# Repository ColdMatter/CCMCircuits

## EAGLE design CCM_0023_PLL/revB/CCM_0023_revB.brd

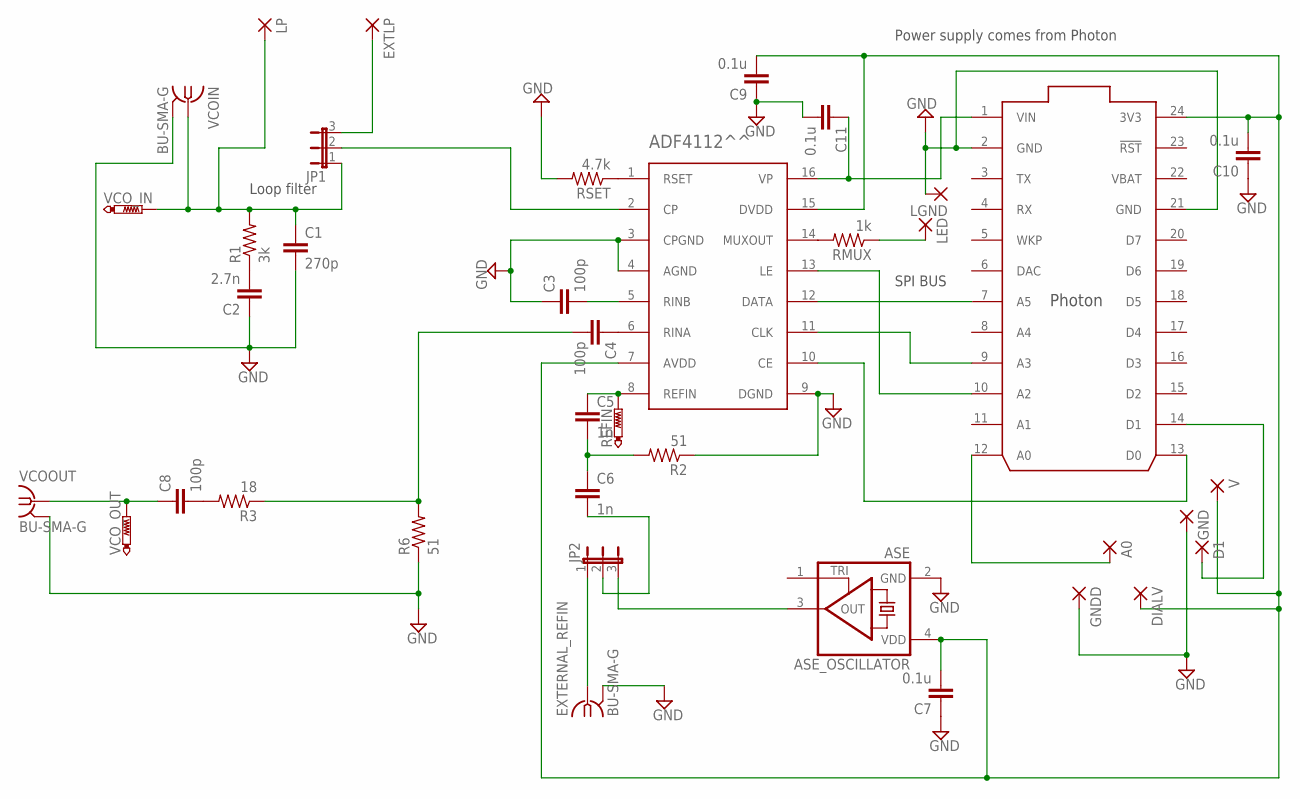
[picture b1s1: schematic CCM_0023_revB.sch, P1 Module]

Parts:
A0: 1,6/0,8
ADF4112^^: ADF4112
ASE_OSCILLATOR: ASE
C1: 270p; C0603
C2: 2.7n; C0603
C3, C4, C8: 100p; C0603
C5, C6: 1n; C0603
C7, C9, C10, C11: 0.1u; C0603
D1: 1,6/0,8
DIALV: 1,6/0,8
EXTERNAL_REFIN: BU-SMA-G
EXTLP: 1,6/0,8
GND: 1,6/0,8
GNDD: 1,6/0,8
JP1, JP2: JP2E; JP2
LED: 1,6/0,8
LGND: 1,6/0,8
LP: 1,6/0,8
PHOTON: PHOTON_WITH_HEADERS; PHOTON
R1: 3k; R0603
R2, R6: 51; R0603
R3: 18; R0603
REFIN: PTR1B2,54; B2,54
RMUX: 1k; R0603
RSET: 4.7k; R0603
V: 1,6/0,8
VCOIN: BU-SMA-G
VCOOUT: BU-SMA-G
VCO_IN: PTR1B2,54; B2,54
VCO_OUT: PTR1B2,54; B2,54

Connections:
GND: ADF4112^^.3 (CPGND), ADF4112^^.4 (AGND), ADF4112^^.9 (DGND), ASE_OSCILLATOR.2 (GND), C1.2, C2.1, C3.1, C7.1, C9.1, C10.1, C11.2, EXTERNAL_REFIN.2, EXTERNAL_REFIN.3 (2), EXTERNAL_REFIN.4 (2), EXTERNAL_REFIN.5 (2), GND.1, GNDD.1, LGND.1, PHOTON.2 (GND), PHOTON.21 (GND), R2.1, R6.1, RSET.2, VCOIN.2, VCOIN.3 (2), VCOIN.4 (2), VCOIN.5 (2), VCOOUT.2, VCOOUT.3 (2), VCOOUT.4 (2), VCOOUT.5 (2)
unnamed: ADF4112^^.12 (DATA), PHOTON.7 (A5)
unnamed: ADF4112^^.11 (CLK), PHOTON.9 (A3)
unnamed: ADF4112^^.13 (LE), PHOTON.10 (A2)
unnamed: ADF4112^^.1 (RSET), RSET.1
unnamed: C2.2, R1.1
unnamed: EXTERNAL_REFIN.1, JP2.1
unnamed: ASE_OSCILLATOR.3 (OUT), JP2.3
unnamed: ADF4112^^.8 (REFIN), C5.1, REFIN.TP
unnamed: C5.2, C6.1, R2.2
unnamed: ADF4112^^.5 (RINB), C3.2
unnamed: ADF4112^^.14 (MUXOUT), RMUX.2
unnamed: C8.1, VCOOUT.1, VCO_OUT.TP
unnamed: A0.1, PHOTON.12 (A0)
unnamed: D1.1, PHOTON.14 (D1)
unnamed: ADF4112^^.16 (VP), C11.1, PHOTON.1 (VIN)
unnamed: C8.2, R3.2
unnamed: C4.2, R3.1, R6.2
unnamed: ADF4112^^.6 (RINA), C4.1
unnamed: LED.1, RMUX.1
unnamed: ADF4112^^.7 (AVDD), ADF4112^^.15 (DVDD), ASE_OSCILLATOR.4 (VDD), C7.2, C9.2, C10.2, DIALV.1, PHOTON.24 (3V3), V.1
unnamed: EXTLP.1, JP1.3
unnamed: ADF4112^^.2 (CP), JP1.2
unnamed: ADF4112^^.10 (CE), PHOTON.13 (D0)
unnamed: C1.1, JP1.1, LP.1, R1.2, VCOIN.1, VCO_IN.TP
unnamed: C6.2, JP2.2
VBAT: PHOTON.22 (VBAT)

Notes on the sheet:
Loop filter
SPI BUS
Power supply comes from Photon

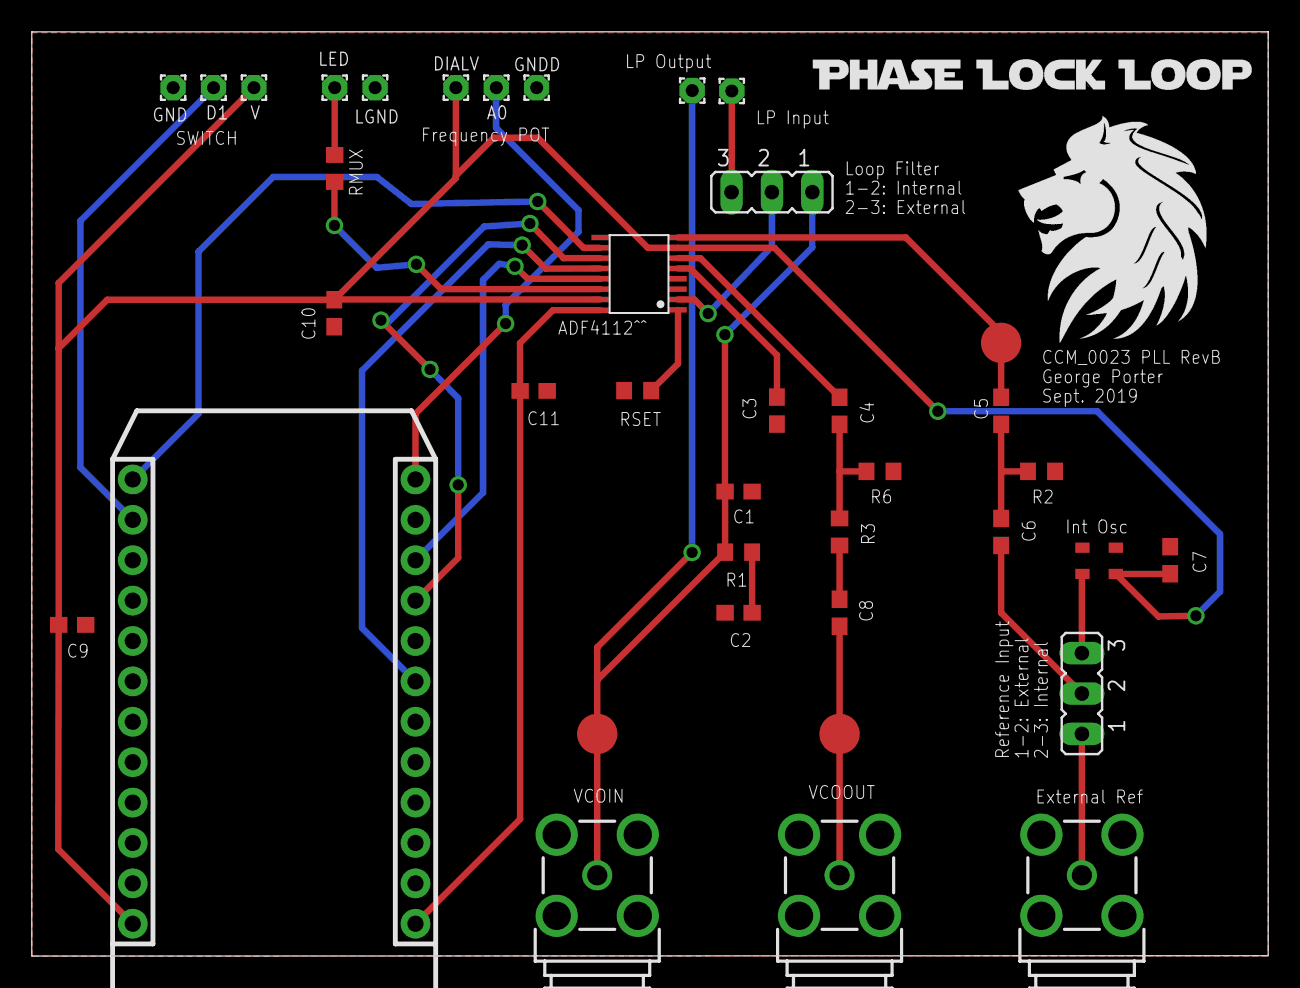
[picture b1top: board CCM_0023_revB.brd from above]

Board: 2 copper layers, 77.8 x 58.1 mm, 38 parts (0 on the bottom side), 26 nets.

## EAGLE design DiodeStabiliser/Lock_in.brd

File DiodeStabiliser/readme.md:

Diode Stabilisation Circuit

This is a work in progress circuit which aims to stabilise a laser diode 
to the centre of its mode. It works by modulating the diode current and 
lock in detecting the increased intensity noise, then feeding back to the 
current to minimise this noise. This works in conjunction with a frequency
lock. It's a copy of the work in Chiow's paper:

Extended-cavity diode lasers with tracked resonances
Sheng-wey Chiow, Quan Long, Christoph Vo, Holger Müller, and Steven Chu  »View Author Affiliations

Applied Optics, Vol. 46, Issue 33, pp. 7997-8001 (2007)
http://dx.doi.org/10.1364/AO.46.007997

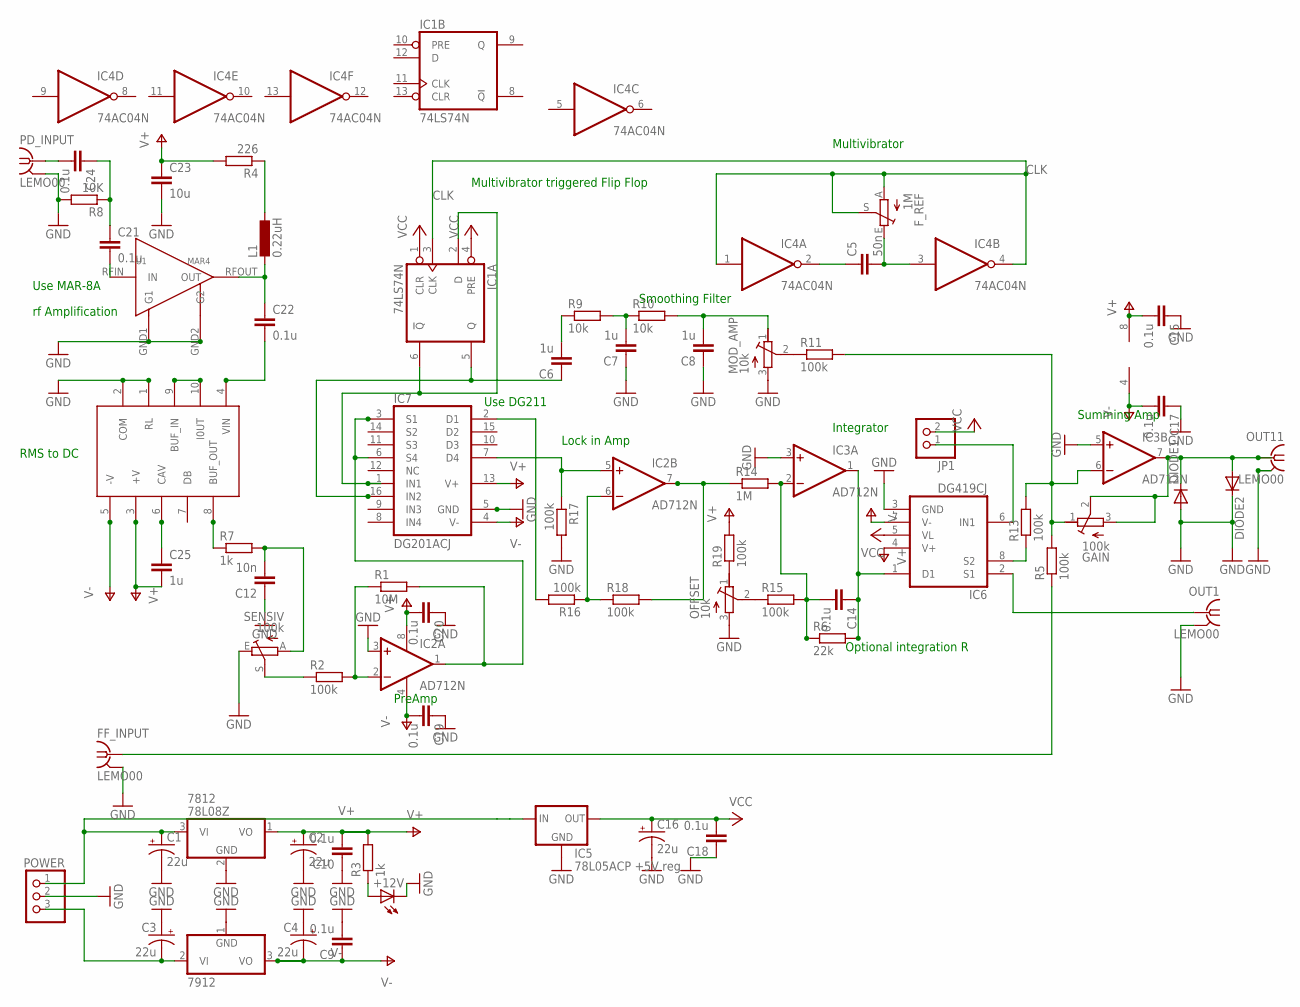
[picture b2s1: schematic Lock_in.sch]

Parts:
7812: 78L08Z; TO92
7912: 79L12Z; TO92
+12V: LED5MM
C1, C2, C3, C4, C16: 22u; E5-4
C5: 50n; C050-024X044
C6, C7, C8: 1u; C050-024X044
C9, C10, C14, C15, C17, C18, C19, C20: 0.1u; C050-024X044
C12: 10n; C050-024X044
C21, C22, C24: 0.1u; C0805
C23: 10u; C1206
C25: 1u; C0805
DIODE1, DIODE2: 1N4004; DO41-10
FF_INPUT: LEMO00; LEMOPAC.PAC
F_REF: 1M; S63P
GAIN: 100k; RTRIM43P
IC1: 74LS74N; DIL14
IC2, IC3: AD712N; DIL08
IC4: 74AC04N; DIL14
IC5: 78L05ACP +5V reg; 78LXX
IC6: DG419CJ; DIL08
IC7: DG201ACJ; DIL16
JP1: PINHD-1X2; 1X02
L1: 0.22uH; L3216C
MOD_AMP: 10k; RTRIM43P
OFFSET: 10k; RTRIM43P
OUT1, OUT11: LEMO00; LEMOPAC.PAC
PD_INPUT: LEMO00; LEMOPAC.PAC
POWER: PINHD-1X3; 1X03
R1: 10M; 0204/7
R2, R5, R11, R13, R15, R16, R17, R18, R19: 100k; 0204/7
R3, R7: 1k; 0204/7
R4: 226; R1206
R6: 22k; 0204/7
R8: 10K; R1206
R9, R10: 10k; 0204/7
R14: 1M; 0204/7
SENSIV: 100k; S63P
U1: MAR4; VV105
U$1: AD636; TO100

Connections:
CLK: F_REF.A, F_REF.S, IC1.3 (CLK), IC4.1 (I), IC4.4 (O)
F2: C6.1, IC1.5 (Q), IC7.16 (IN2)
GND: 7812.2 (GND), 7912.1 (GND), +12V.K (C), C1.-, C2.-, C3.+, C4.+, C7.1, C8.1, C9.2, C10.1, C12.1, C15.1, C16.-, C17.1, C18.1, C19.1, C20.1, C23.2, DIODE1.A, DIODE2.C, FF_INPUT.2 (GND), FF_INPUT.3 (GND), FF_INPUT.4 (GND), FF_INPUT.5 (GND), IC1.7 (GND), IC2.3 (+IN), IC3.3 (+IN), IC3.5 (+IN), IC4.7 (GND), IC5.GND, IC6.3 (GND), IC7.5 (GND), MOD_AMP.3 (E), OFFSET.3 (E), OUT1.2 (GND), OUT1.3 (GND), OUT1.4 (GND), OUT1.5 (GND), OUT11.2 (GND), OUT11.3 (GND), OUT11.4 (GND), OUT11.5 (GND), PD_INPUT.2 (GND), PD_INPUT.3 (GND), PD_INPUT.4 (GND), PD_INPUT.5 (GND), POWER.2, R8.2, R17.2, SENSIV.E, U1.GND1 (G1), U1.GND2 (G2), U$1.1 (RL), U$1.2 (COM)
GND1: IC6.6 (IN1), JP1.1
MOD_AMPLITUDE: C8.2, MOD_AMP.1 (A), R10.2
unnamed: C5.1, IC4.2 (O)
unnamed: +12V.A, R3.1
unnamed: DIODE1.C, DIODE2.A, GAIN.2 (S), GAIN.3 (E), IC3.7 (OUT), OUT11.1
unnamed: IC2.2 (-IN), R1.1, R2.2
unnamed: C5.2, F_REF.E, IC4.3 (I)
unnamed: R2.1, SENSIV.S
unnamed: C12.2, R7.2, SENSIV.A
unnamed: R7.1, U$1.8 (BUF_OUT)
unnamed: C6.2, R9.1
unnamed: C7.2, R9.2, R10.1
unnamed: GAIN.1 (A), IC3.6 (-IN), R5.2, R11.2, R13.2
unnamed: MOD_AMP.2 (S), R11.1
unnamed: IC2.1 (OUT), IC7.3 (S1), IC7.6 (S4), R1.2
unnamed: OFFSET.1 (A), R19.1
unnamed: IC6.8 (S2), R13.1
unnamed: IC1.2 (D), IC1.6 (!Q), IC7.1 (IN1)
unnamed: C14.2, IC3.2 (-IN), R6.1, R14.2, R15.2
unnamed: IC7.2 (D1), R16.2
unnamed: IC2.5 (+IN), IC7.7 (D4), R17.1
unnamed: IC2.6 (-IN), R16.1, R18.1
unnamed: IC2.7 (OUT), R14.1, R18.2
unnamed: OFFSET.2 (S), R15.1
unnamed: C21.2, U1.RFIN (IN)
unnamed: C14.1, IC3.1 (OUT), IC6.1 (D1), R6.2
unnamed: L1.1, R4.1
unnamed: C22.1, L1.2, U1.RFOUT (OUT)
unnamed: C24.2, PD_INPUT.1
unnamed: C21.1, C24.1, R8.1
unnamed: C22.2, U$1.4 (VIN)
unnamed: IC6.2 (S1), OUT1.1
unnamed: U$1.9 (BUF_IN), U$1.10 (I0UT)
unnamed: C25.1, U$1.6 (CAV)
OUT: FF_INPUT.1, R5.1
V+: 7812.1 (VO), C2.+, C10.2, C15.2, C20.2, C23.1, C25.2, IC2.8 (V+), IC3.8 (V+), IC6.4 (V+), IC7.13 (V+), R3.2, R4.2, R19.2, U$1.3 (+V)
V+INPUT: 7812.3 (VI), C1.+, IC5.IN, POWER.1
V-: 7912.3 (VO), C4.-, C9.1, C17.2, C19.2, IC2.4 (V-), IC3.4 (V-), IC6.7 (V-), IC7.4 (V-), U$1.5 (-V)
V-INPUT: 7912.2 (VI), C3.-, POWER.3
VCC: C16.+, C18.2, IC1.1 (CLR), IC1.4 (PRE), IC1.14 (VCC), IC4.14 (VCC), IC5.OUT, IC6.5 (VL), JP1.2

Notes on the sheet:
Multivibrator
PreAmp
Lock in Amp
Smoothing Filter
Summing Amp
Integrator
rf Amplification
RMS to DC
Multivibrator triggered Flip Flop
Use MAR-8A
Optional integration R
Use DG211

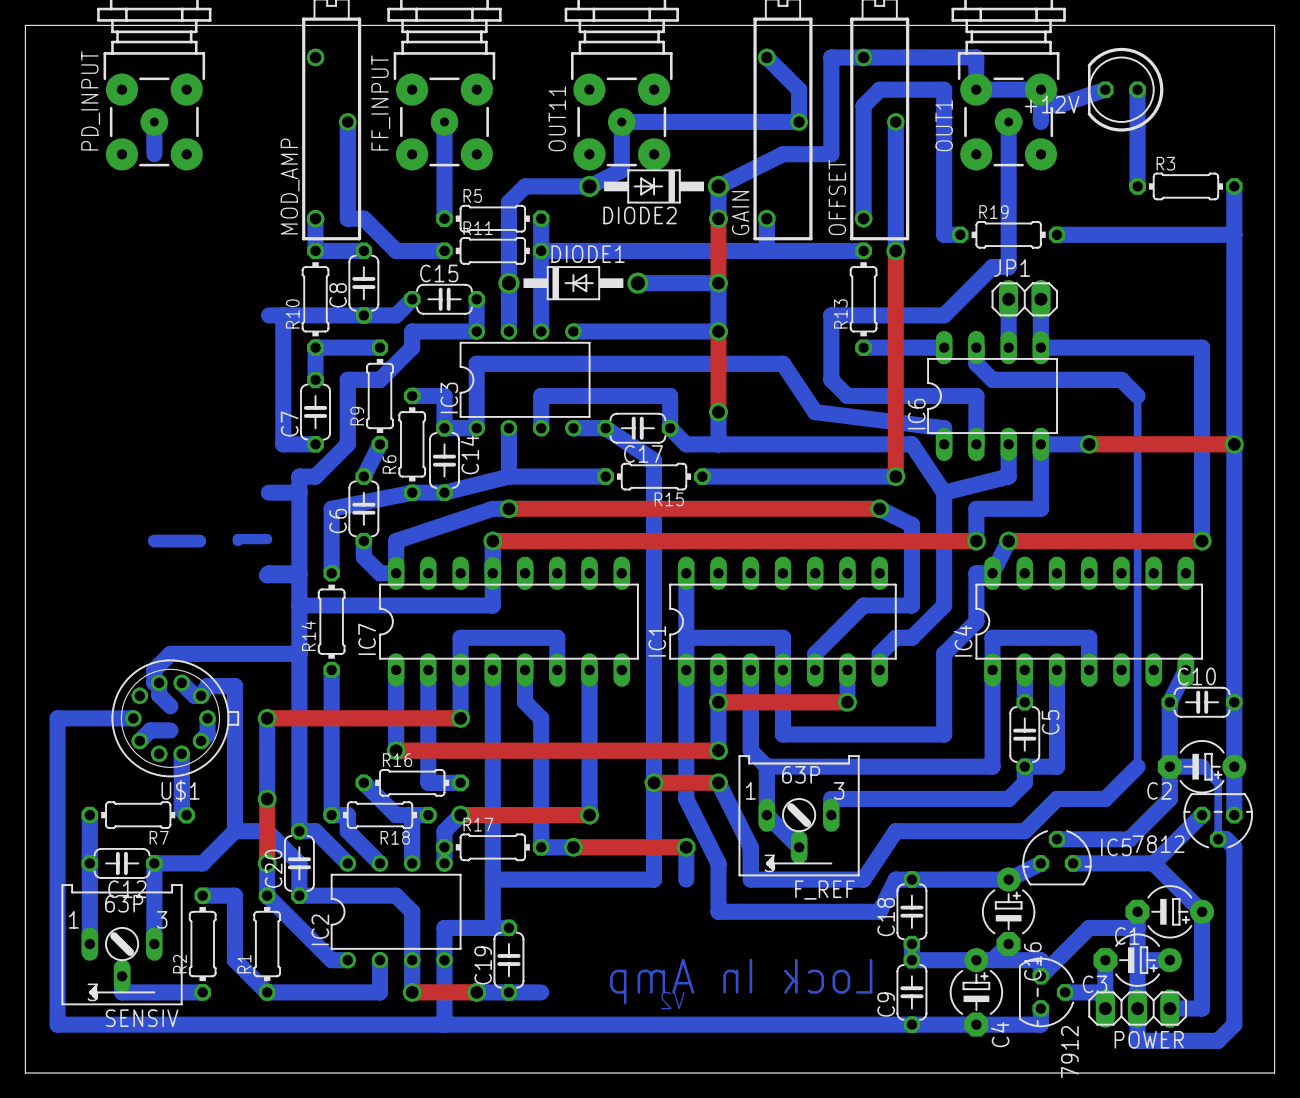
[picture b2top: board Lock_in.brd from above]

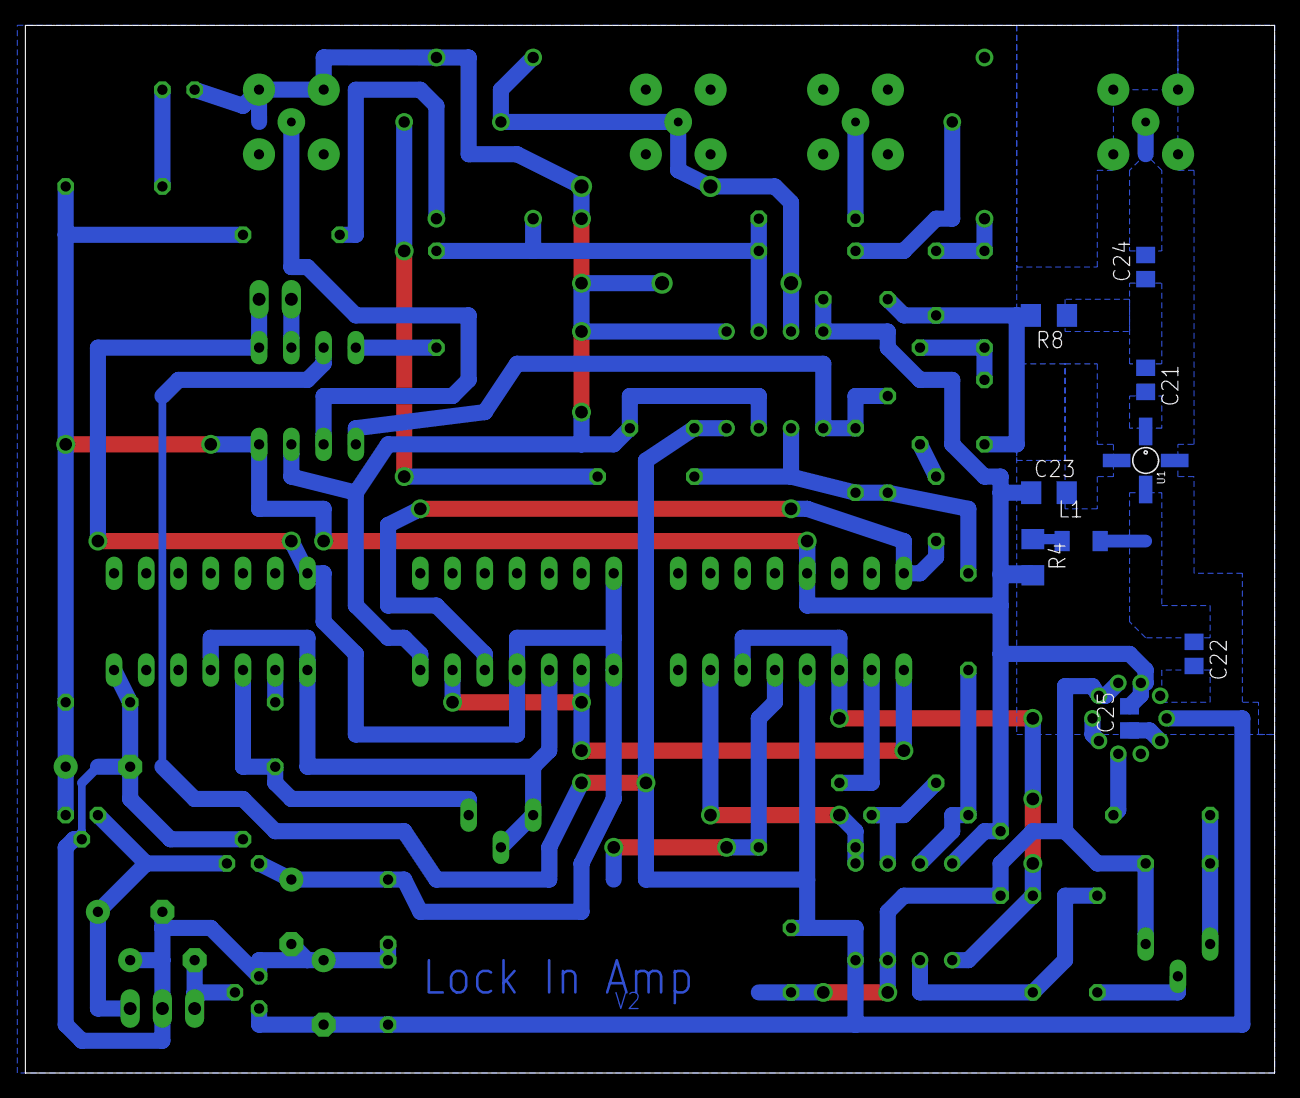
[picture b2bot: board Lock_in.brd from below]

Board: 2 copper layers, 98.4 x 82.5 mm, 67 parts (9 on the bottom side), 43 nets.

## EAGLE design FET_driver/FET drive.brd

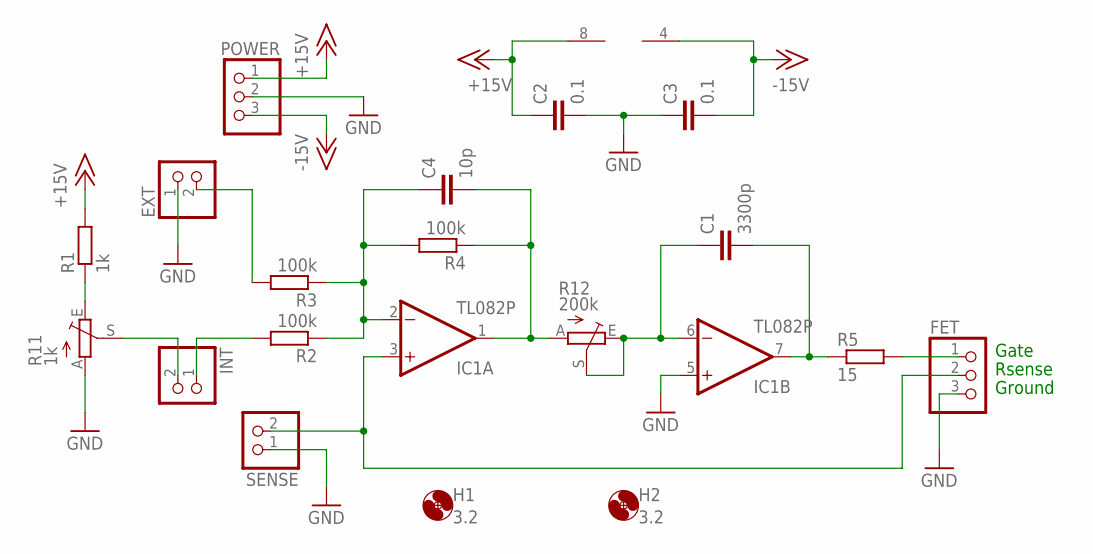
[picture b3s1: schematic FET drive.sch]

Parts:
C1: 3300p; C025-025X050
C2, C3: 0.1; C025-025X050
C4: 10p; C025-025X050
EXT: PINHD-1X2; 1X02
FET: PINHD-1X3; 1X03
H1, H2: 3.2; 3,2
IC1: TL082P; DIL08
INT: PINHD-1X2; 1X02
POWER: PINHD-1X3; 1X03
R1: 1k; R0805
R2, R3, R4: 100k; R0805
R5: 15; 0204/5
R11: 1k; B25P
R12: 200k; B25P
SENSE: PINHD-1X2; 1X02

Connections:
+15V: C2.1, IC1.8 (V+), POWER.1, R1.2
-15V: C3.2, IC1.4 (V-), POWER.3
GND: C2.2, C3.1, EXT.1, FET.3, IC1.5 (+IN), POWER.2, R11.A, SENSE.1
unnamed: R1.1, R11.E
unnamed: INT.2, R11.S
unnamed: INT.1, R2.2
unnamed: EXT.2, R3.2
unnamed: C4.1, IC1.2 (-IN), R2.1, R3.1, R4.2
unnamed: C4.2, IC1.1 (OUT), R4.1, R12.A
unnamed: C1.1, IC1.6 (-IN), R12.E, R12.S
unnamed: C1.2, IC1.7 (OUT), R5.1
unnamed: FET.1, R5.2
unnamed: FET.2, IC1.3 (+IN), SENSE.2

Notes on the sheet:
Gate
Rsense
Ground

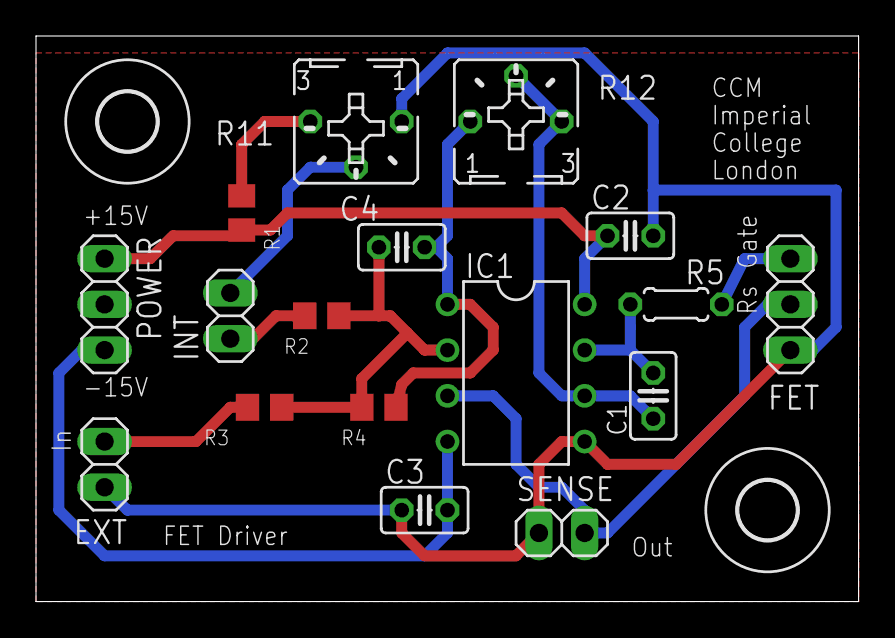
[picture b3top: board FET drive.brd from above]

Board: 2 copper layers, 45.7 x 31.4 mm, 19 parts (0 on the bottom side), 13 nets.

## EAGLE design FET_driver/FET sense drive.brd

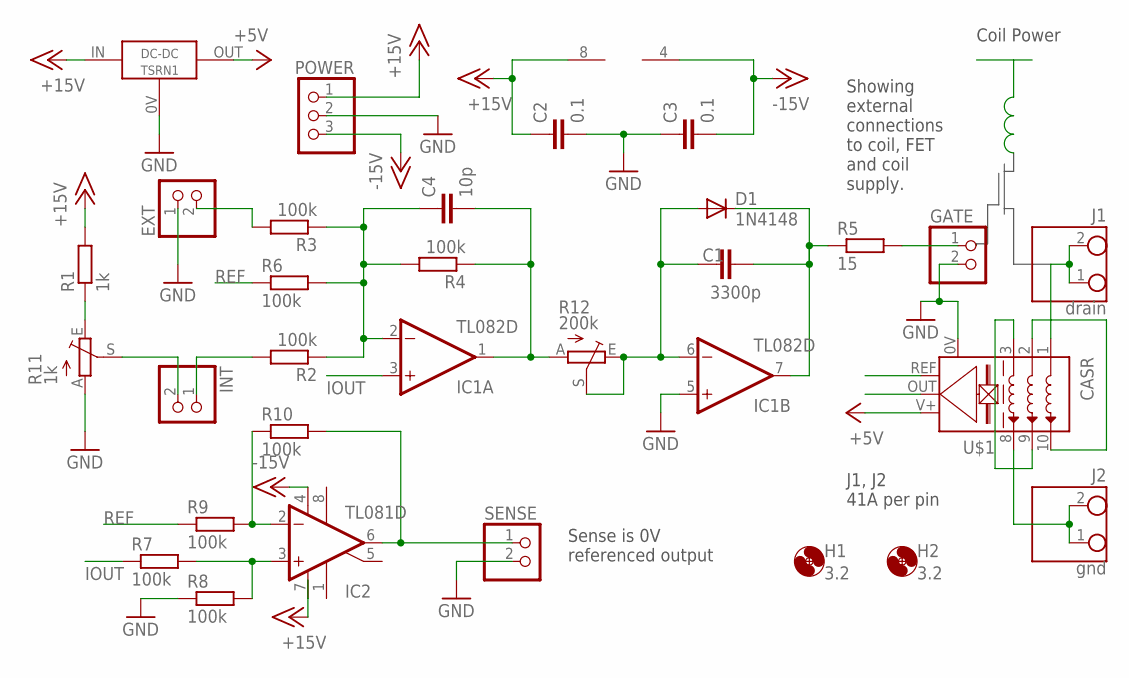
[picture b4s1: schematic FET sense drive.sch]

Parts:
C1: 3300p; C025-025X050
C2, C3: 0.1; C0805
C4: 10p; C025-025X050
D1: 1N4148; SOD323_ST
DC-DC: TSRN1; TSRN1X
EXT: PINHD-1X2; 1X02
GATE: PINHD-1X2; 1X02
H1, H2: 3.2; 3,2
IC1: TL082D; SO08
IC2: TL081D; SO08
INT: PINHD-1X2; 1X02
J1: drain; PHL
J2: gnd; PHL
POWER: PINHD-1X3; 1X03
R1: 1k; R0805
R2, R3, R4, R6, R7, R8, R9, R10: 100k; R0805
R5: 15; 0204/5
R11: 1k; B25P
R12: 200k; B25P
SENSE: PINHD-1X2; 1X02
U$1: CASR

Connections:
+5V: DC-DC.OUT, U$1.V+
+15V: C2.1, DC-DC.IN, IC1.8 (V+), POWER.1, R1.2
-15V: C3.2, IC1.4 (V-), IC2.4 (V-), POWER.3
GND: C2.2, C3.1, DC-DC.0V, EXT.1, GATE.2, IC1.5 (+IN), POWER.2, R8.1, R11.A, SENSE.2, U$1.0V
IOUT: IC1.3 (+IN), R7.1, U$1.OUT (VOUT)
unnamed: R1.1, R11.E
unnamed: INT.2, R11.S
unnamed: INT.1, R2.2
unnamed: EXT.2, R3.2
unnamed: C4.1, IC1.2 (-IN), R2.1, R3.1, R4.2, R6.2
unnamed: J1.1, J1.2, U$1.1 (IN1)
unnamed: C4.2, IC1.1 (OUT), R4.1, R12.A
unnamed: C1.1, D1.A, IC1.6 (-IN), R12.E, R12.S
unnamed: C1.2, D1.C, IC1.7 (OUT), R5.1
unnamed: GATE.1, R5.2
unnamed: IC2.3 (+IN), R7.2, R8.2
unnamed: U$1.2 (IN2), U$1.10 (OUT10)
unnamed: J2.1, J2.2, U$1.8 (OUT8)
unnamed: U$1.3 (IN3), U$1.9 (OUT9)
unnamed: IC2.2 (-IN), R9.2, R10.1
unnamed: IC2.6 (OUT), R10.2, SENSE.1
REF: R6.1, R9.1, U$1.REF (VREF)
V+: IC2.7 (V+)

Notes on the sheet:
Coil Power
Showing external connections to coil, FET and coil supply.
Sense is 0V referenced output
J1, J2 41A per pin

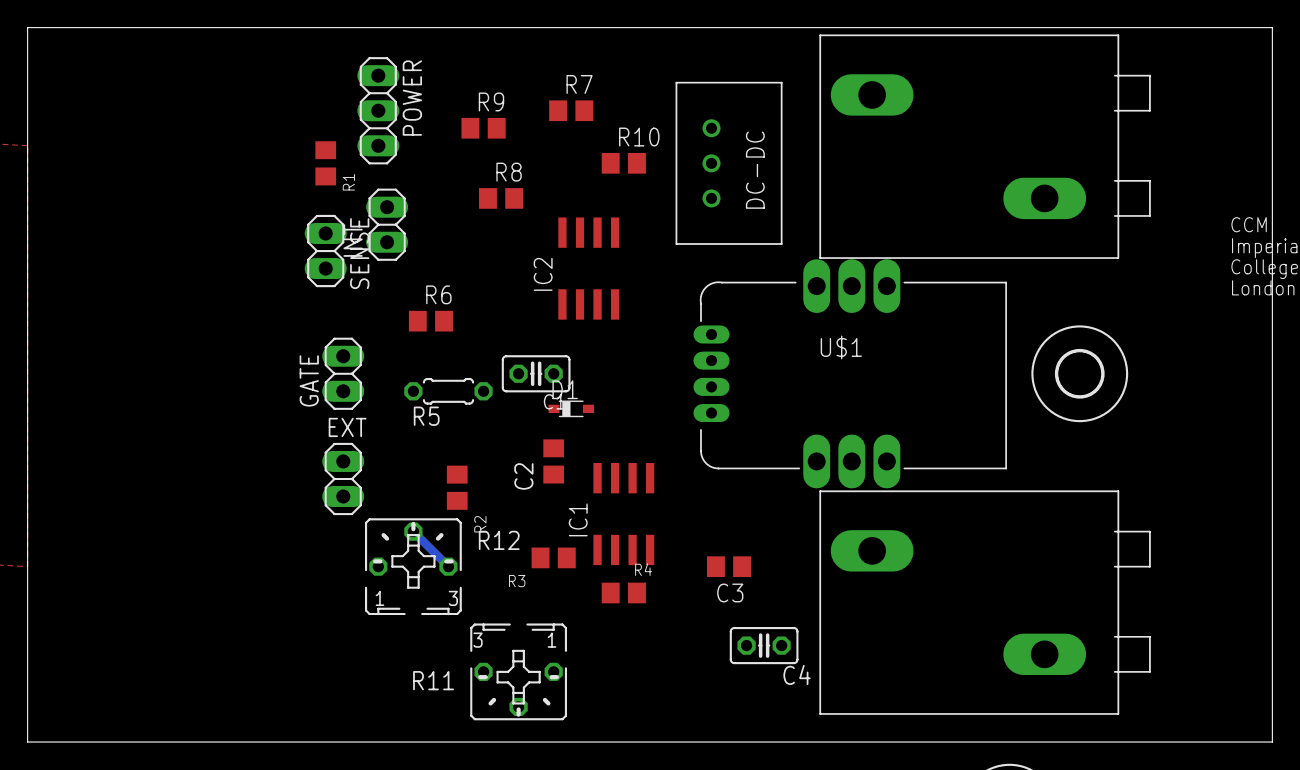
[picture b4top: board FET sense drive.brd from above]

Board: 2 copper layers, 90.2 x 51.7 mm, 30 parts (0 on the bottom side), 22 nets.

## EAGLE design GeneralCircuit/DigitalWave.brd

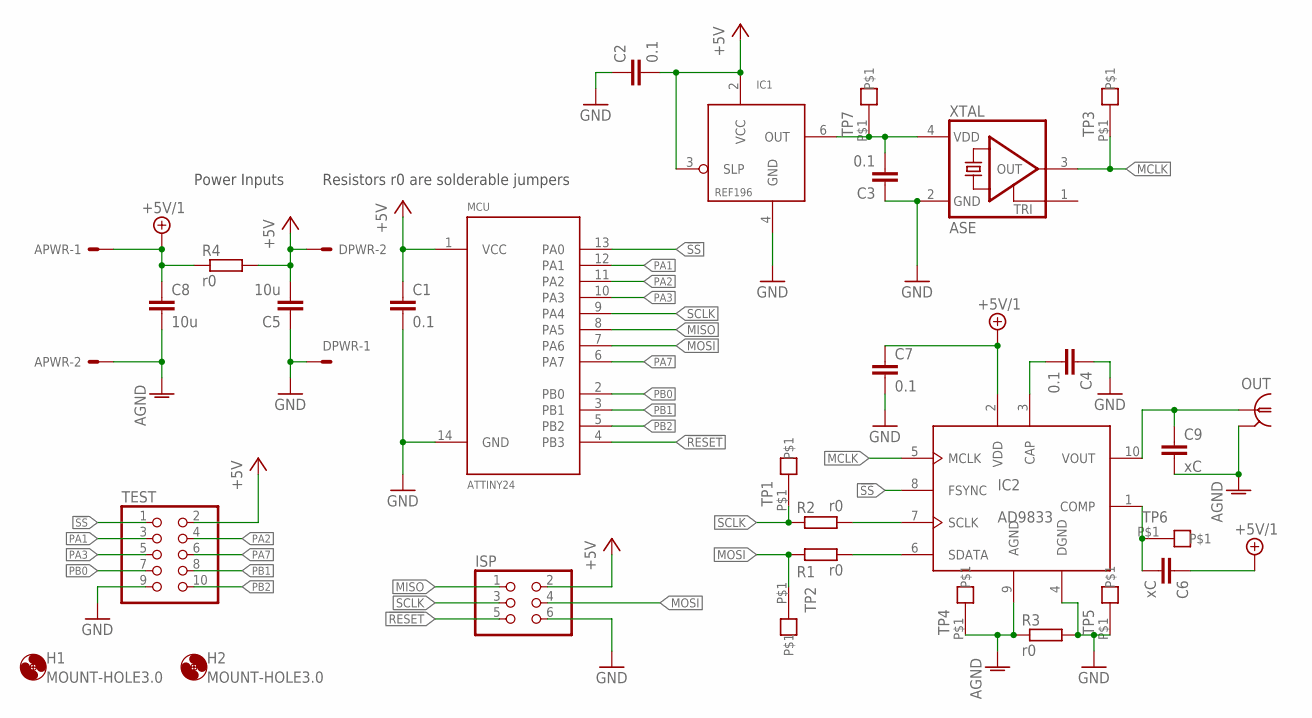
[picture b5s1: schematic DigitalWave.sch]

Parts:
APWR: 22-27-2021-02; 6410-02
C1: 0.1; C0805
C2, C3, C4, C7: 0.1; C0603
C5, C8: 10u; C0805
C6, C9: xC; C0805
DPWR: 22-27-2021-02; 6410-02
H1, H2: MOUNT-HOLE3.0; 3,0
IC1: REF196; SO08
IC2: AD9833; MSOP10
ISP: PINHD-2X3; 2X03
MCU: ATTINY24; SO14
OUT: LTI-SASF54GT
R1, R2, R3, R4: r0; R0402
TEST: PINHD-2X5; 2X05
TP1, TP2, TP3, TP4, TP5, TP6, TP7: TESTPOINT
XTAL: ASE

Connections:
3.3: C3.2, IC1.6 (OUT), TP7.P$1, XTAL.4 (VDD)
!RESET: ISP.5, MCU.4 (PB3)
!SS: IC2.8 (FSYNC), MCU.13 (PA0), TEST.1
+5V: C1.1, C2.2, C5.2, DPWR.2, IC1.2 (VCC), IC1.3 (SLP), ISP.2, MCU.1 (VCC), R4.2, TEST.2
+5V/1: APWR.1, C6.1, C7.1, C8.1, IC2.2 (VDD), R4.1
AGND: APWR.2, C8.2, C9.2, IC2.9 (AGND), OUT.2, OUT.3 (2), OUT.4 (2), OUT.5 (2), R3.1, TP4.P$1
COMP: C6.2, IC2.1 (COMP), TP6.P$1
GND: C1.2, C2.1, C3.1, C4.1, C5.1, C7.2, DPWR.1, IC1.4 (GND), IC2.4 (DGND), ISP.6, MCU.14 (GND), R3.2, TEST.9, TP5.P$1, XTAL.2 (GND)
MCLK: IC2.5 (MCLK), TP3.P$1, XTAL.3 (OUT)
MISO: ISP.1, MCU.8 (PA5)
MOSI: ISP.4, MCU.7 (PA6), R1.1, TP2.P$1
unnamed: IC2.6 (SDATA), R1.2
unnamed: IC2.7 (SCLK), R2.2
unnamed: C4.2, IC2.3 (CAP)
OUT: C9.1, IC2.10 (VOUT), OUT.1
PA1: MCU.12 (PA1), TEST.3
PA2: MCU.11 (PA2), TEST.4
PA3: MCU.10 (PA3), TEST.5
PA7: MCU.6 (PA7), TEST.6
PB0: MCU.2 (PB0), TEST.7
PB1: MCU.3 (PB1), TEST.8
PB2: MCU.5 (PB2), TEST.10
SCLK: ISP.3, MCU.9 (PA4), R2.1, TP1.P$1

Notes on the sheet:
Power Inputs
Resistors r0 are solderable jumpers

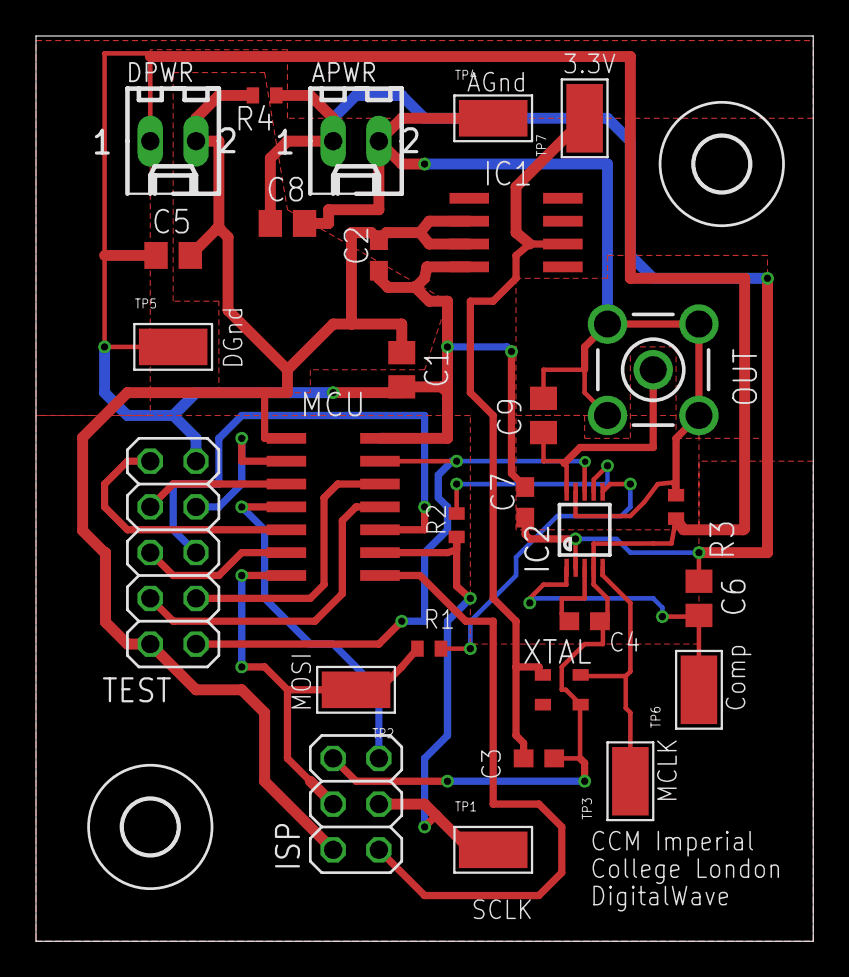
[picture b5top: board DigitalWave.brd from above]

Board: 2 copper layers, 43.2 x 50.3 mm, 31 parts (0 on the bottom side), 23 nets.

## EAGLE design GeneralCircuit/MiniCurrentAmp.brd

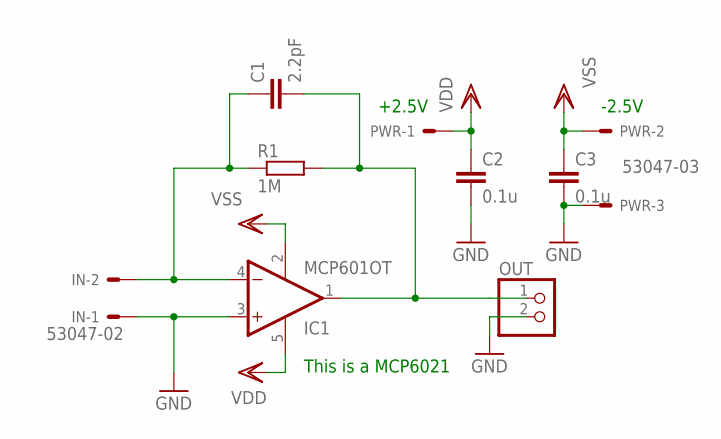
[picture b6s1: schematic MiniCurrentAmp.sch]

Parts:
C1: 2.2pF; C0805
C2, C3: 0.1u; C0805
IC1: MCP601OT; SOT23-5
IN: 53047-02
OUT: PINHD-1X2; 1X02
PWR: 53047-03
R1: 1M; R0805

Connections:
GND: C2.2, C3.2, IC1.3 (+IN), IN.1, OUT.2, PWR.3
unnamed: C1.1, IC1.4 (-IN), IN.2, R1.1
unnamed: C1.2, IC1.1 (OUT), OUT.1, R1.2
VDD: C2.1, IC1.5 (V+), PWR.1
VSS: C3.1, IC1.2 (V-), PWR.2

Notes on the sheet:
This is a MCP6021
+2.5V
-2.5V

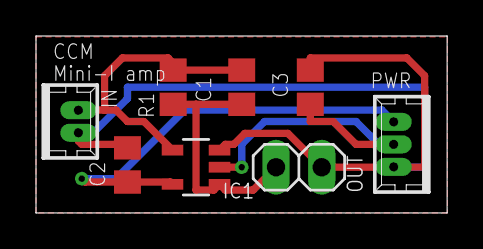
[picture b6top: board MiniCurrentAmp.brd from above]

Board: 2 copper layers, 22.8 x 9.8 mm, 8 parts (0 on the bottom side), 5 nets.

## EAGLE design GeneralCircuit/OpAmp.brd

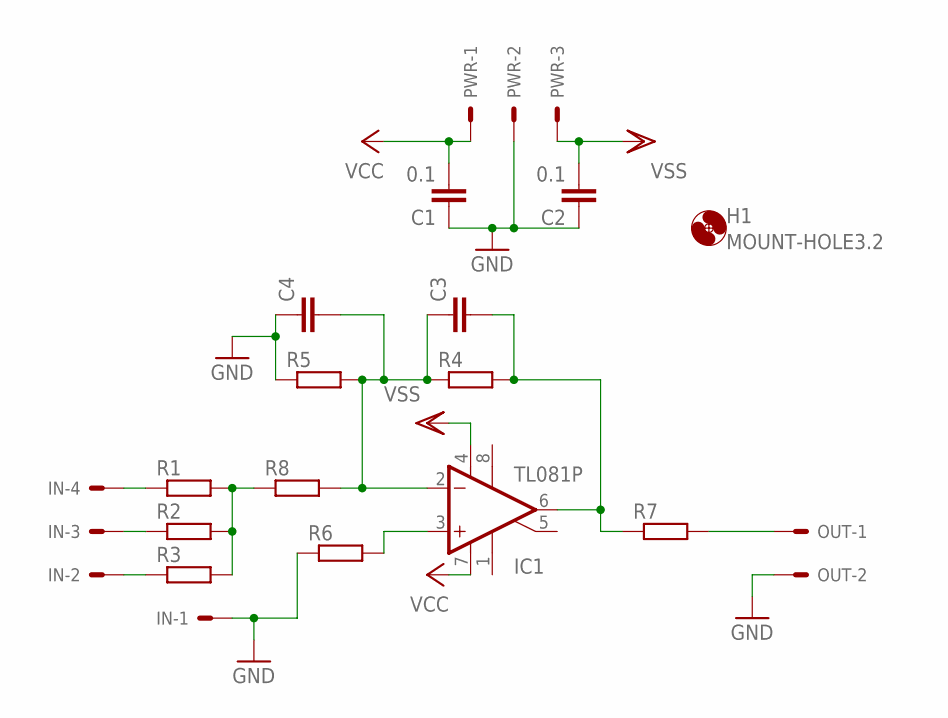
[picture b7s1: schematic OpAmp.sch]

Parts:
C1, C2: 0.1; C050-030X075
C3, C4: C-EU050-030X075; C050-030X075
H1: MOUNT-HOLE3.2; 3,2
IC1: TL081P; DIL08
IN: 22-27-2041-04; 6410-04
OUT: 22-27-2021-02; 6410-02
PWR: 22-27-2031-03; 6410-03
R1, R2, R3, R4, R5, R6, R7, R8: R-EU_0204/7; 0204/7

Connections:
GND: C1.1, C2.1, C4.1, IN.1, OUT.2, PWR.2, R5.1, R6.1
unnamed: IN.4, R1.1
unnamed: IN.3, R2.1
unnamed: IN.2, R3.1
unnamed: C3.1, C4.2, IC1.2 (-IN), R4.1, R5.2, R8.2
unnamed: C3.2, IC1.6 (OUT), R4.2, R7.1
unnamed: OUT.1, R7.2
unnamed: IC1.3 (+IN), R6.2
unnamed: R1.2, R2.2, R3.2, R8.1
VCC: C1.2, IC1.7 (V+), PWR.1
VSS: C2.2, IC1.4 (V-), PWR.3

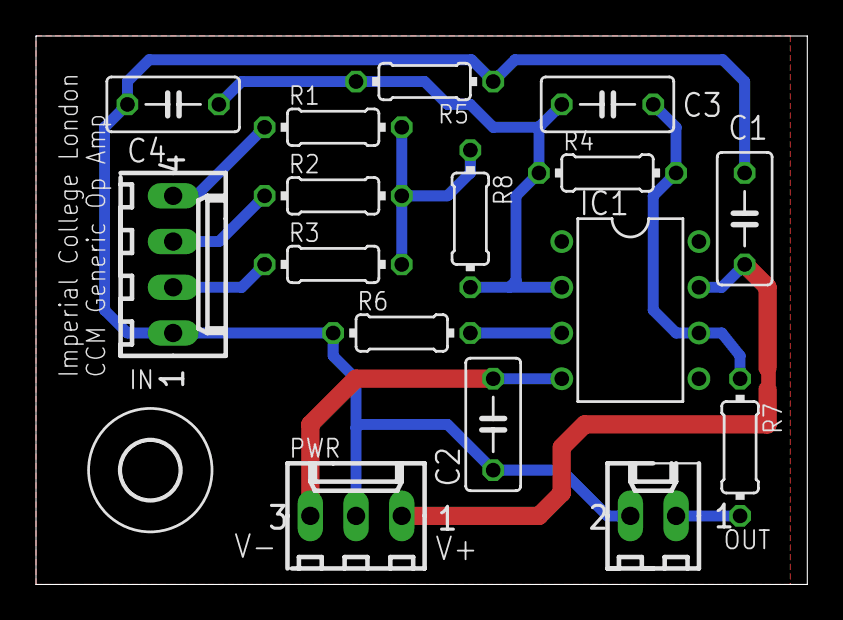
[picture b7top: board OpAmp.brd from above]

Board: 2 copper layers, 42.9 x 30.5 mm, 17 parts (0 on the bottom side), 11 nets.

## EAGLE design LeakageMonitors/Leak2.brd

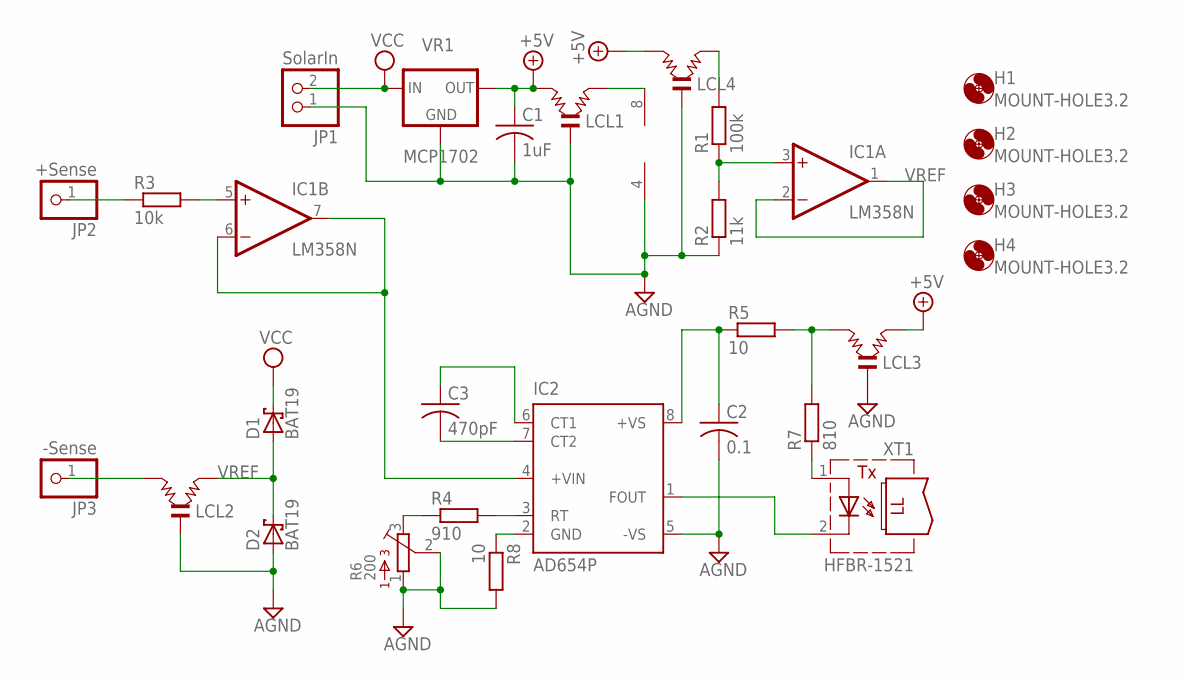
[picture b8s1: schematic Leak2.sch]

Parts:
C1: 1uF; C050-035X075
C2: 0.1; C050-035X075
C3: 470pF; C050-035X075
D1, D2: BAT19; DO35-10
H1, H2, H3, H4: MOUNT-HOLE3.2; 3,2
IC1: LM358N; DIL08
IC2: AD654P; DIL08
JP1: SolarIn; 1X02
JP2: +Sense; 1X01
JP3: -Sense; 1X01
LCL1, LCL2, LCL3, LCL4: LCL
R1: 100k; 0204/7
R2: 11k; 0204/7
R3: 10k; 0204/7
R4: 910; 0204/7
R5, R8: 10; 0204/7
R6: 200; 3386F
R7: 810; 0204/7
VR1: MCP1702; TO92-
XT1: HFBR-1521; HFBR-15X3

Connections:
+5V: C1.1, LCL1.1, LCL3.2, LCL4.1, VR1.1 (OUT)
AGND: C1.2, C2.2, D2.A, IC1.4 (V-), IC2.5 (-VS), JP1.1, LCL1.0 (GND), LCL2.0 (GND), LCL3.0 (GND), LCL4.0 (GND), R2.1, R6.1, R6.2, R8.2, VR1.3 (GND)
unnamed: JP2.1, R3.1
unnamed: IC1.5 (+IN), R3.2
unnamed: IC1.6 (-IN), IC1.7 (OUT), IC2.4 (+VIN)
unnamed: IC1.8 (V+), LCL1.2
unnamed: IC1.3 (+IN), R1.1, R2.2
unnamed: IC2.3 (RT), R4.2
unnamed: JP3.1, LCL2.1
unnamed: C2.1, IC2.8 (+VS), R5.1
unnamed: C3.2, IC2.7 (CT2)
unnamed: C3.1, IC2.6 (CT1)
unnamed: R4.1, R6.3
unnamed: IC2.1 (FOUT), XT1.2 (C)
unnamed: LCL3.1, R5.2, R7.2
unnamed: R7.1, XT1.1 (A)
unnamed: IC2.2 (GND), R8.1
unnamed: LCL4.2, R1.2
VCC: D1.C, JP1.2, VR1.2 (IN)
VREF: D1.A, D2.C, IC1.1 (OUT), IC1.2 (-IN), LCL2.2

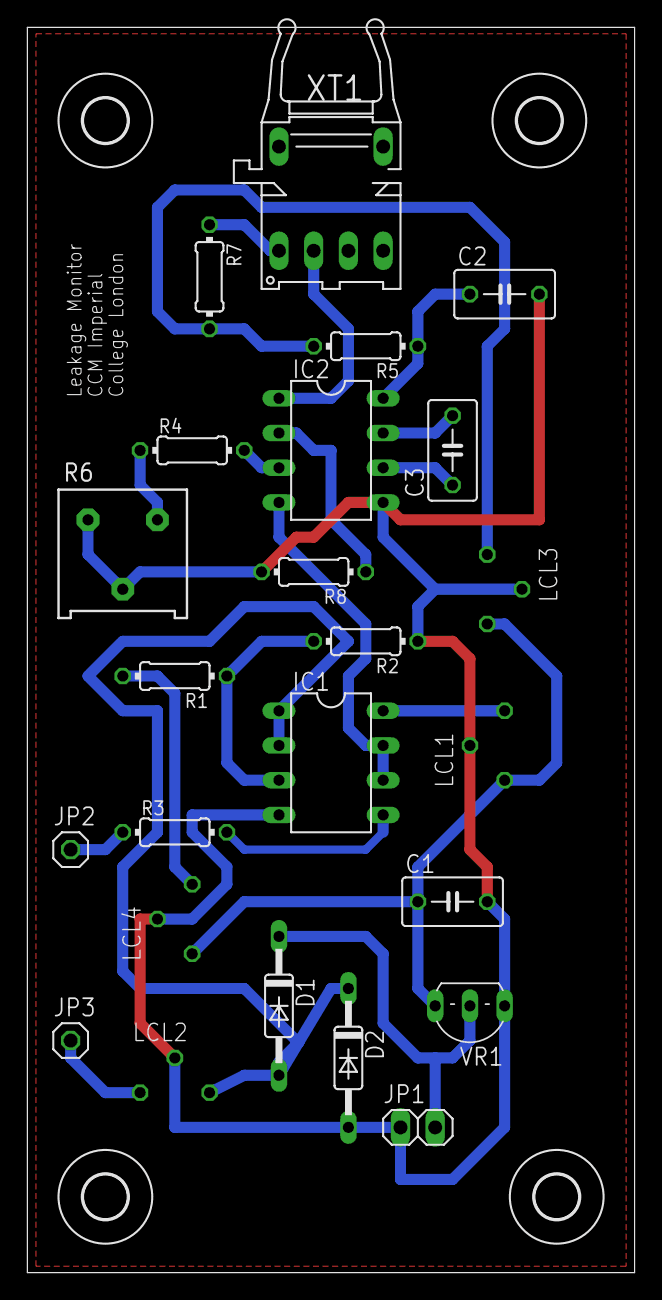
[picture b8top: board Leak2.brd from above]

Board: 2 copper layers, 44.4 x 91.1 mm, 28 parts (0 on the bottom side), 20 nets.
